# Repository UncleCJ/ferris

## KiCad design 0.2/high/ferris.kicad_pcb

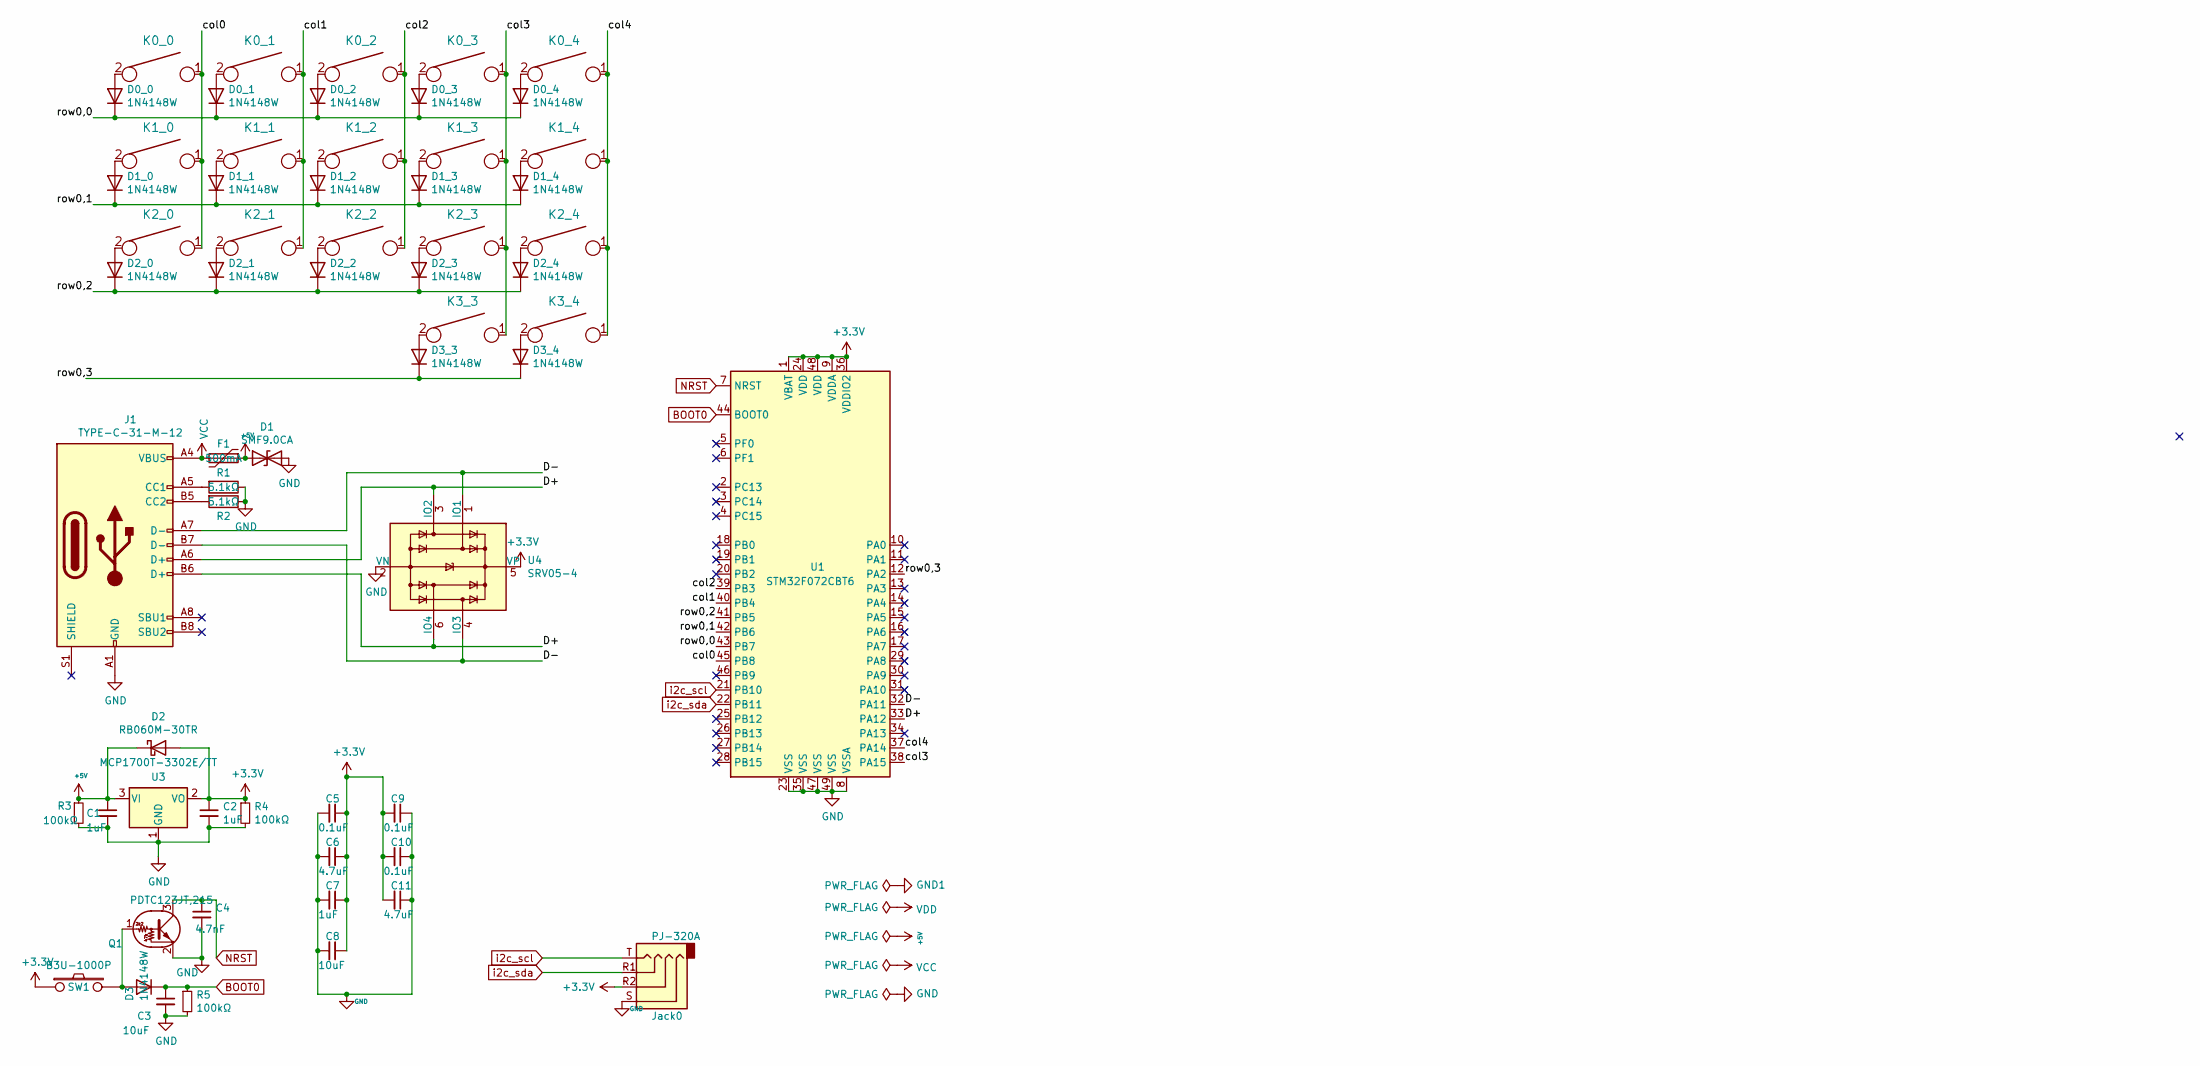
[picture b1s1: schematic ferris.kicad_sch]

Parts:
C1, C2, C7: 1uF; C_0805_2012Metric_Pad1.15x1.40mm_HandSolder; Part Name Capacitor; LCSC Part C28323
C3, C8: 10uF; C_0805_2012Metric_Pad1.15x1.40mm_HandSolder; Part Name Capacitor; LCSC Part C17024
C4: 4.7nF; C_0805_2012Metric_Pad1.15x1.40mm_HandSolder; Part Name Capacitor; LCSC Part C717014
C5, C9, C10: 0.1uF; C_0805_2012Metric_Pad1.15x1.40mm_HandSolder; Part Name Capacitor; LCSC Part C49678
C6, C11: 4.7uF; C_0805_2012Metric_Pad1.15x1.40mm_HandSolder; Part Name Capacitor; LCSC Part C87998
D0_0, D0_1, D0_2, D0_3, D0_4, D1_0, D1_1, D1_2, D1_3, D1_4, D2_0, D2_1, D2_2, D2_3, D2_4, D3, D3_3, D3_4: 1N4148W; D_SOD-123; Part Name Diode; LCSC Part C81598
D1: SMF9.0CA; D_SOD-123; Part Name Bidirectional Diode; LCSC Part C435473
D2: RB060M-30TR; D_SOD-123; Part Name Schottky Barrier Diode; LCSC Part C559324
F1: 500mA; Fuse_1206_3216Metric; Part Name Polyfuse; LCSC Part C151162
J1: TYPE-C-31-M-12; USB_C_Receptacle_HRO_TYPE-C-31-M-12; Part Name USB C; LCSC Part C165948
Jack0: PJ-320A; TRRS-PJ-320A; Part Name TRRS Jack; LCSC Part C12569
K0_0, K0_1, K0_2, K0_3, K0_4, K1_0, K1_1, K1_2, K1_3, K1_4, K2_0, K2_1, K2_2, K2_3, K2_4, K3_3, K3_4: KEYSW; MX; Part Name Key; JLCPCB BOM false
Q1: PDTC123JT,215; SOT-23; Part Name NPN Transistor; LCSC Part C406040
R1, R2: 5.1kΩ; R_0805_2012Metric_Pad1.15x1.40mm_HandSolder; Part Name Resistor; LCSC Part C27834
R3, R4, R5: 100kΩ; R_0805_2012Metric_Pad1.15x1.40mm_HandSolder; Part Name Resistor; LCSC Part C149504
SW1: B3U-1000P; SW_SPST_B3U-1000P; Part Name Reset; LCSC Part C231329
U1: STM32F072CBT6; Dual_MCU_QFP_QFN_48_with_breakout_pins; Part Name MCU; LCSC Part C81720
U3: MCP1700T-3302E/TT; SOT-23; Part Name Dropout Regulator; LCSC Part C39051
U4: SRV05-4; SOT-23-6; Part Name TVS Diode Array; LCSC Part C558418

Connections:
+3V3: C2.1, C5.1, C6.1, C7.1, C8.1, C9.2, C10.2, C11.2, D2.2 (A), Jack0.R2, R4.1, SW1.1, U1.1 (VBAT), U1.9 (VDDA), U1.24 (VDD), U1.36 (VDDIO2), U1.48 (VDD), U3.2 (VO), U4.5 (VP)
+5V: C1.1, D1.1 (A1), D2.1 (K), F1.1, R3.1, U3.3 (VI)
/D+: J1.A6 (D+), J1.B6 (D+), U1.33 (PA12), U4.3 (IO2), U4.6 (IO4)
/D-: J1.A7 (D-), J1.B7 (D-), U1.32 (PA11), U4.1 (IO1), U4.4 (IO3)
/col0: K0_0.1, K1_0.1, K2_0.1, U1.45 (PB8)
/col1: K0_1.1, K1_1.1, K2_1.1, U1.40 (PB4)
/col2: K0_2.1, K1_2.1, K2_2.1, U1.39 (PB3)
/col3: K0_3.1, K1_3.1, K2_3.1, K3_3.1, U1.38 (PA15)
/col4: K0_4.1, K1_4.1, K2_4.1, K3_4.1, U1.37 (PA14)
/row0,0: D0_0.1 (K), D0_1.1 (K), D0_2.1 (K), D0_3.1 (K), D0_4.1 (K), U1.43 (PB7)
/row0,1: D1_0.1 (K), D1_1.1 (K), D1_2.1 (K), D1_3.1 (K), D1_4.1 (K), U1.42 (PB6)
/row0,2: D2_0.1 (K), D2_1.1 (K), D2_2.1 (K), D2_3.1 (K), D2_4.1 (K), U1.41 (PB5)
/row0,3: D3_3.1 (K), D3_4.1 (K), U1.12 (PA2)
BOOT0: C3.1, D3.1 (K), R5.1, U1.44 (BOOT0)
GND: C1.2, C2.2, C3.2, C4.2, C5.2, C6.2, C7.2, C8.2, C9.1, C10.1, C11.1, D1.2 (A2), J1.A1 (GND), J1.A12 (GND), J1.B1 (GND), J1.B12 (GND), Jack0.S, Q1.2 (E), R1.1, R2.1, R3.2, R4.2, R5.2, U1.8 (VSSA), U1.23 (VSS), U1.35 (VSS), U1.47 (VSS), U1.49 (VSS), U3.1 (GND), U4.2 (VN)
NRST: C4.1, Q1.3 (C), U1.7 (NRST)
unnamed: D0_0.2 (A), K0_0.2
unnamed: D0_1.2 (A), K0_1.2
unnamed: D0_2.2 (A), K0_2.2
unnamed: D0_3.2 (A), K0_3.2
unnamed: D0_4.2 (A), K0_4.2
unnamed: D1_0.2 (A), K1_0.2
unnamed: D1_1.2 (A), K1_1.2
unnamed: D1_2.2 (A), K1_2.2
unnamed: D1_3.2 (A), K1_3.2
unnamed: D1_4.2 (A), K1_4.2
unnamed: D2_0.2 (A), K2_0.2
unnamed: D2_1.2 (A), K2_1.2
unnamed: D2_2.2 (A), K2_2.2
unnamed: D2_3.2 (A), K2_3.2
unnamed: D2_4.2 (A), K2_4.2
unnamed: D3.2 (A), Q1.1 (B), SW1.2
unnamed: D3_3.2 (A), K3_3.2
unnamed: D3_4.2 (A), K3_4.2
unnamed: J1.A5 (CC1), R1.2
unnamed: J1.B5 (CC2), R2.2
VCC: F1.2, J1.A4 (VBUS), J1.A9 (VBUS), J1.B4 (VBUS), J1.B9 (VBUS)
i2c_scl: Jack0.T, U1.21 (PB10)
i2c_sda: Jack0.R1, U1.22 (PB11)

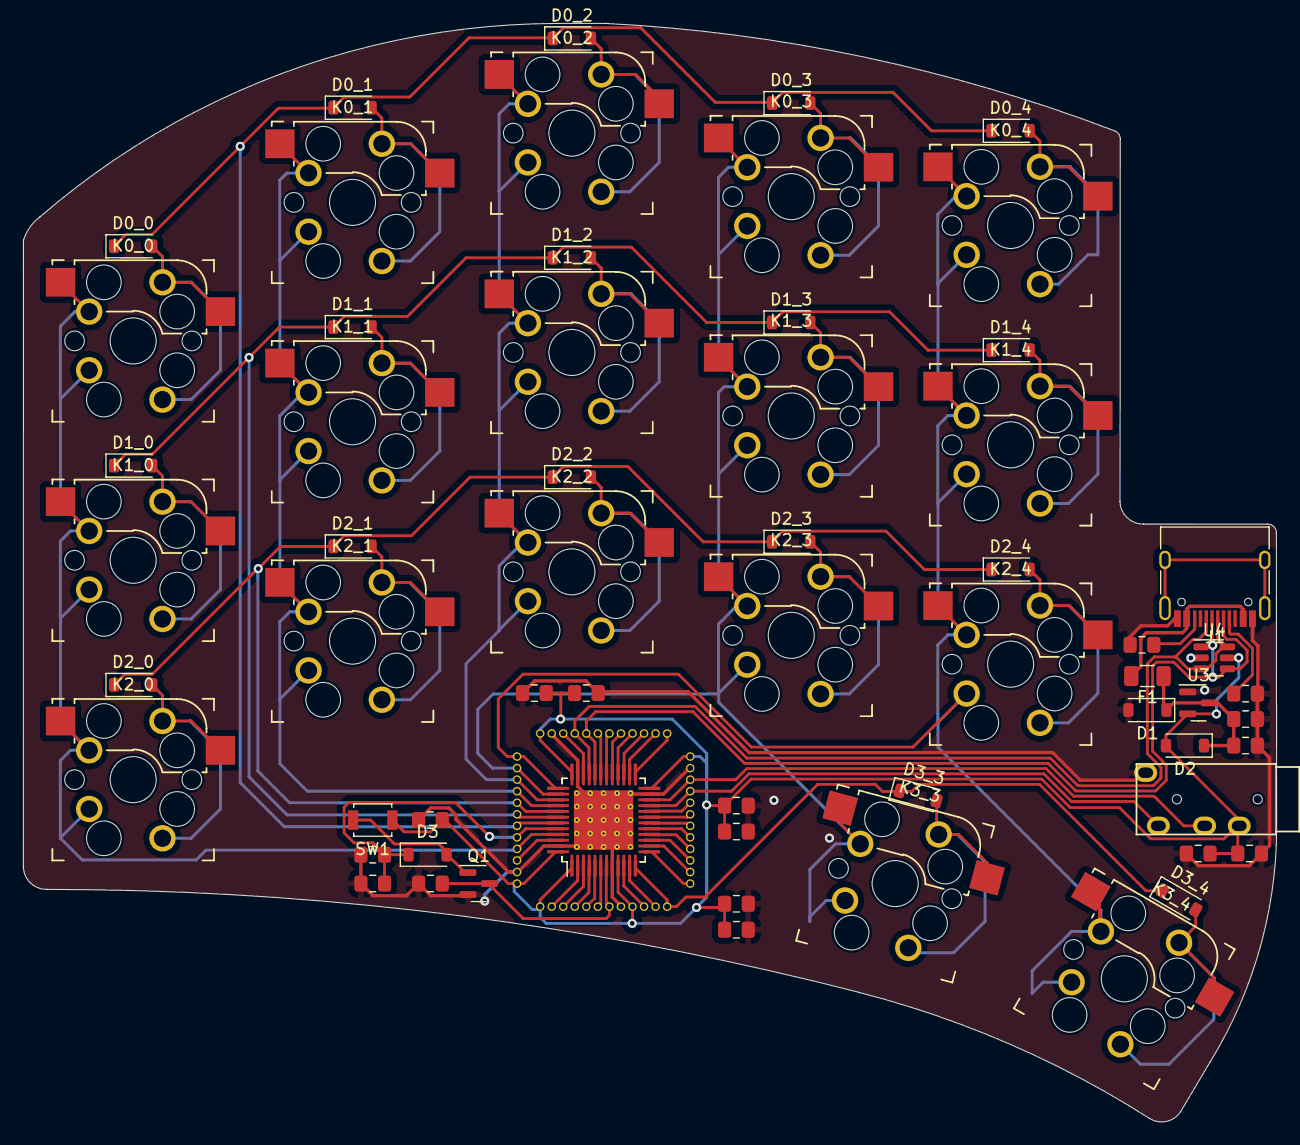
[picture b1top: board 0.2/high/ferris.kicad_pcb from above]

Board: 2 copper layers, 108.5 x 95.2 mm, 61 parts (0 on the bottom side), 39 nets.

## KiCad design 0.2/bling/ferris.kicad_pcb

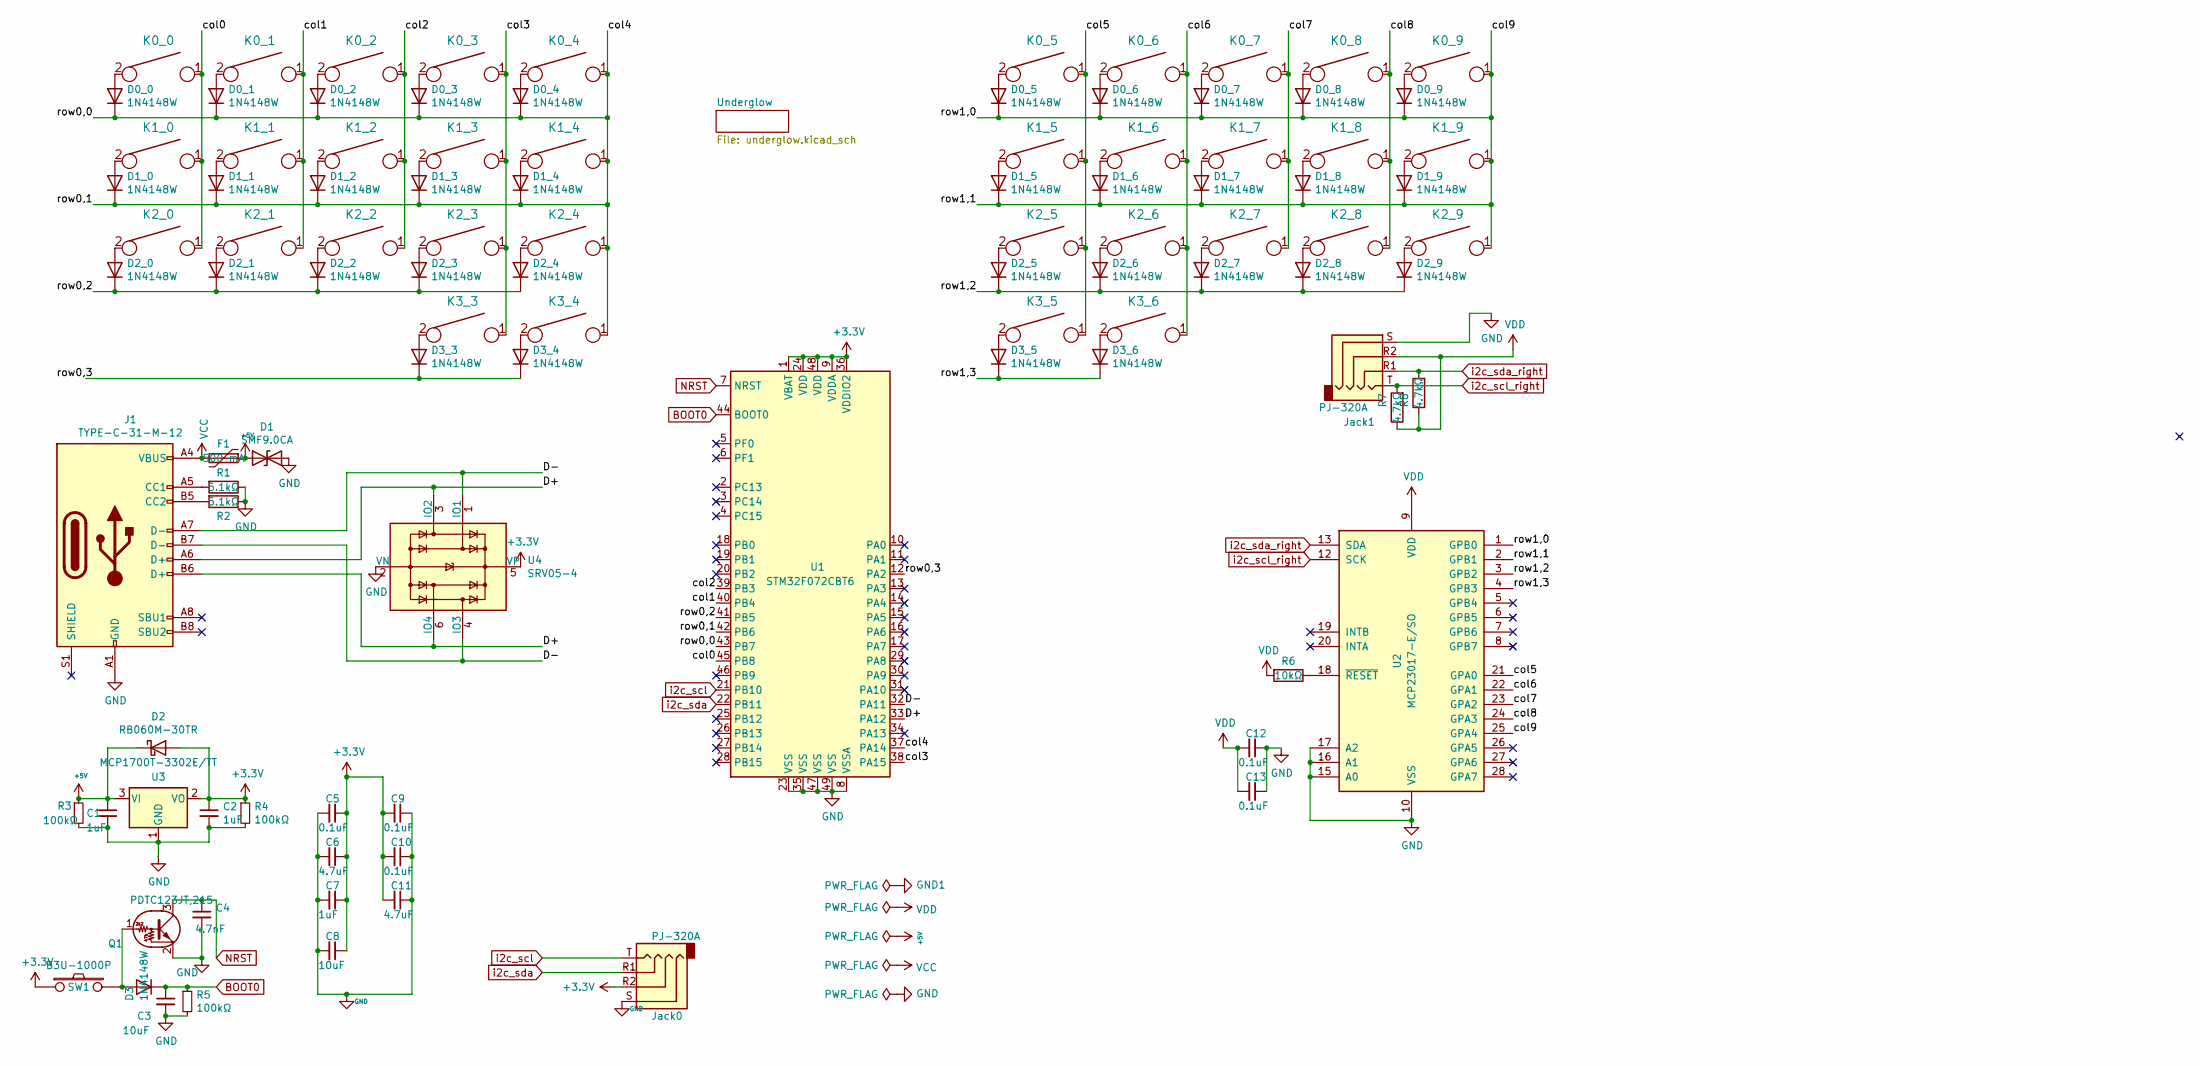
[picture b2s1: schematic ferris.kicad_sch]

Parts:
C1, C2, C7: 1uF; C_0805_2012Metric_Pad1.15x1.40mm_HandSolder; Part Name Capacitor; LCSC Part C28323
C3, C8: 10uF; C_0805_2012Metric_Pad1.15x1.40mm_HandSolder; Part Name Capacitor; LCSC Part C17024
C4: 4.7nF; C_0805_2012Metric_Pad1.15x1.40mm_HandSolder; Part Name Capacitor; LCSC Part C717014
C5, C9, C10, C12, C13: 0.1uF; C_0805_2012Metric_Pad1.15x1.40mm_HandSolder; Part Name Capacitor; LCSC Part C49678
C6, C11: 4.7uF; C_0805_2012Metric_Pad1.15x1.40mm_HandSolder; Part Name Capacitor; LCSC Part C87998
D0_0, D0_1, D0_2, D0_3, D0_4, D0_5, D0_6, D0_7, D0_8, D0_9, D1_0, D1_1, D1_2, D1_3, D1_4, D1_5, D1_6, D1_7, D1_8, D1_9, D2_0, D2_1, D2_2, D2_3, D2_4, D2_5, D2_6, D2_7, D2_8, D2_9, D3, D3_3, D3_4, D3_5, D3_6: 1N4148W; D_SOD-123; Part Name Diode; LCSC Part C81598
D1: SMF9.0CA; D_SOD-123; Part Name Bidirectional Diode; LCSC Part C435473
D2: RB060M-30TR; D_SOD-123; Part Name Schottky Barrier Diode; LCSC Part C559324
F1: 500 mA; Fuse_1206_3216Metric; Part Name Polyfuse; LCSC Part C151162
J1: TYPE-C-31-M-12; USB_C_Receptacle_HRO_TYPE-C-31-M-12; Part Name USB C; LCSC Part C165948
Jack0, Jack1: PJ-320A; TRRS-PJ-320A; Part Name TRRS Jack; LCSC Part C12569
K0_0, K0_1, K0_2, K0_3, K0_4, K0_5, K0_6, K0_7, K0_8, K0_9, K1_0, K1_1, K1_2, K1_3, K1_4, K1_5, K1_6, K1_7, K1_8, K1_9, K2_0, K2_1, K2_2, K2_3, K2_4, K2_5, K2_6, K2_7, K2_8, K2_9, K3_3, K3_4, K3_5, K3_6: KEYSW; Choc_PG1350_Choc_Spacing; Part Name Key; JLCPCB BOM false
Q1: PDTC123JT,215; SOT-23; Part Name NPN Transistor; LCSC Part C406040
R1, R2: 5.1kΩ; R_0805_2012Metric_Pad1.15x1.40mm_HandSolder; Part Name Resistor; LCSC Part C27834
R3, R4, R5: 100kΩ; R_0805_2012Metric_Pad1.15x1.40mm_HandSolder; Part Name Resistor; LCSC Part C149504
R6: 10kΩ; R_0805_2012Metric_Pad1.15x1.40mm_HandSolder; Part Name Resistor; LCSC Part C17414
R7, R8: 4.7kΩ; R_0805_2012Metric_Pad1.15x1.40mm_HandSolder; Part Name Resistor; LCSC Part C17673
SW1: B3U-1000P; SW_SPST_B3U-1000P; Part Name Reset; LCSC Part C231329
U1: STM32F072CBT6; Dual_MCU_QFP_QFN_48_with_breakout_pins; Part Name MCU; LCSC Part C81720
U2: MCP23017-E/SO; SOIC-28W_7.5x17.9mm_P1.27mm; Part Name I/O Expander; LCSC Part C47023
U3: MCP1700T-3302E/TT; SOT-23; Part Name Dropout Regulator; LCSC Part C39051
U4: SRV05-4; SOT-23-6; Part Name TVS Diode Array; LCSC Part C558418

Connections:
+3V3: C2.1, C5.1, C6.1, C7.1, C8.1, C9.2, C10.2, C11.2, D2.2 (A), Jack0.R2, R4.1, SW1.1, U1.1 (VBAT), U1.9 (VDDA), U1.24 (VDD), U1.36 (VDDIO2), U1.48 (VDD), U3.2 (VO), U4.5 (VP); also elsewhere on the board
+5V: C1.1, D1.1 (A1), D2.1 (K), F1.1, R3.1, U3.3 (VI)
/D+: J1.A6 (D+), J1.B6 (D+), U1.33 (PA12), U4.3 (IO2), U4.6 (IO4)
/D-: J1.A7 (D-), J1.B7 (D-), U1.32 (PA11), U4.1 (IO1), U4.4 (IO3)
/col0: K0_0.1, K1_0.1, K2_0.1, U1.45 (PB8)
/col1: K0_1.1, K1_1.1, K2_1.1, U1.40 (PB4)
/col2: K0_2.1, K1_2.1, K2_2.1, U1.39 (PB3)
/col3: K0_3.1, K1_3.1, K2_3.1, K3_3.1, U1.38 (PA15)
/col5: K0_5.1, K1_5.1, K2_5.1, K3_5.1, U2.21 (GPA0)
/col6: K0_6.1, K1_6.1, K2_6.1, K3_6.1, U2.22 (GPA1)
/col7: K0_7.1, K1_7.1, K2_7.1, U2.23 (GPA2)
/col8: K0_8.1, K1_8.1, K2_8.1, U2.24 (GPA3)
/row0,2: D2_0.1 (K), D2_1.1 (K), D2_2.1 (K), D2_3.1 (K), D2_4.1 (K), U1.41 (PB5)
/row0,3: D3_3.1 (K), D3_4.1 (K), U1.12 (PA2)
/row1,2: D2_5.1 (K), D2_6.1 (K), D2_7.1 (K), D2_8.1 (K), D2_9.1 (K), U2.3 (GPB2)
/row1,3: D3_5.1 (K), D3_6.1 (K), U2.4 (GPB3)
BOOT0: C3.1, D3.1 (K), R5.1, U1.44 (BOOT0)
GND: C1.2, C2.2, C3.2, C4.2, C5.2, C6.2, C7.2, C8.2, C9.1, C10.1, C11.1, C12.1, C13.1, D1.2 (A2), J1.A1 (GND), J1.A12 (GND), J1.B1 (GND), J1.B12 (GND), Jack0.S, Jack1.S, Q1.2 (E), R1.1, R2.1, R3.2, R4.2, R5.2, U1.8 (VSSA), U1.23 (VSS), U1.35 (VSS), U1.47 (VSS), U1.49 (VSS), U2.10 (VSS), U2.15 (A0), U2.16 (A1), U2.17 (A2), U3.1 (GND), U4.2 (VN); also elsewhere on the board
NRST: C4.1, Q1.3 (C), U1.7 (NRST)
unnamed: D0_0.2 (A), K0_0.2
unnamed: D0_1.2 (A), K0_1.2
unnamed: D0_2.2 (A), K0_2.2
unnamed: D0_3.2 (A), K0_3.2
unnamed: D0_4.2 (A), K0_4.2
unnamed: D0_5.2 (A), K0_5.2
unnamed: D0_6.2 (A), K0_6.2
unnamed: D0_7.2 (A), K0_7.2
unnamed: D0_8.2 (A), K0_8.2
unnamed: D0_9.2 (A), K0_9.2
unnamed: D1_0.2 (A), K1_0.2
unnamed: D1_1.2 (A), K1_1.2
unnamed: D1_2.2 (A), K1_2.2
unnamed: D1_3.2 (A), K1_3.2
unnamed: D1_4.2 (A), K1_4.2
unnamed: D1_5.2 (A), K1_5.2
unnamed: D1_6.2 (A), K1_6.2
unnamed: D1_7.2 (A), K1_7.2
unnamed: D1_8.2 (A), K1_8.2
unnamed: D1_9.2 (A), K1_9.2
unnamed: D2_0.2 (A), K2_0.2
unnamed: D2_1.2 (A), K2_1.2
unnamed: D2_2.2 (A), K2_2.2
unnamed: D2_3.2 (A), K2_3.2
unnamed: D2_4.2 (A), K2_4.2
unnamed: D2_5.2 (A), K2_5.2
unnamed: D2_6.2 (A), K2_6.2
unnamed: D2_7.2 (A), K2_7.2
unnamed: D2_8.2 (A), K2_8.2
unnamed: D2_9.2 (A), K2_9.2
unnamed: D3.2 (A), Q1.1 (B), SW1.2
unnamed: D3_3.2 (A), K3_3.2
unnamed: D3_4.2 (A), K3_4.2
unnamed: D3_5.2 (A), K3_5.2
unnamed: D3_6.2 (A), K3_6.2
unnamed: J1.A5 (CC1), R1.2
unnamed: J1.B5 (CC2), R2.2
unnamed: R6.1, U2.18 (~RESET)
VCC: F1.2, J1.A4 (VBUS), J1.A9 (VBUS), J1.B4 (VBUS), J1.B9 (VBUS)
VDD: C12.2, C13.2, Jack1.R2, R6.2, R7.1, R8.1, U2.9 (VDD); also elsewhere on the board
i2c_scl: Jack0.T, U1.21 (PB10); also elsewhere on the board
i2c_scl_right: Jack1.T, R7.2, U2.12 (SCK); also elsewhere on the board
i2c_sda: Jack0.R1, U1.22 (PB11); also elsewhere on the board
i2c_sda_right: Jack1.R1, R8.2, U2.13 (SDA); also elsewhere on the board

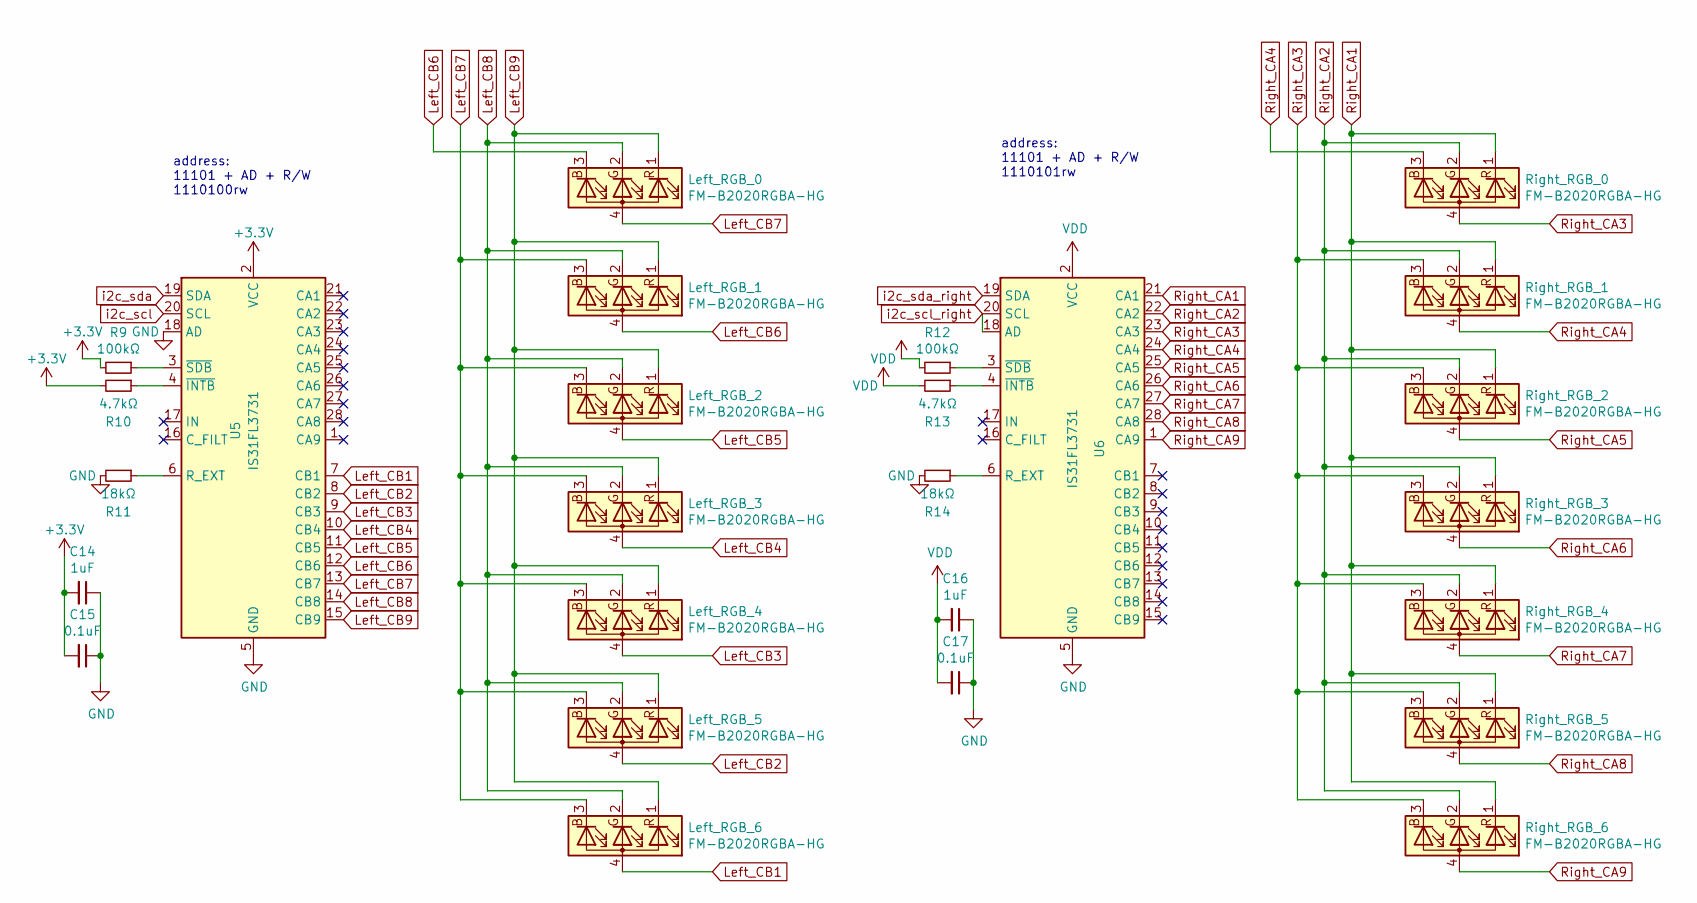
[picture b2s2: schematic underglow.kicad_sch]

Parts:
C14, C16: 1uF; C_0805_2012Metric_Pad1.15x1.40mm_HandSolder; Part Name Capacitor; LCSC Part C28323
C15, C17: 0.1uF; C_0805_2012Metric_Pad1.15x1.40mm_HandSolder; Part Name Capacitor; LCSC Part C49678
Left_RGB_0, Left_RGB_1, Left_RGB_2, Left_RGB_3, Left_RGB_4, Left_RGB_5, Left_RGB_6: FM-B2020RGBA-HG; LED_RGB_FM-B2020RGBA-HG; Part Name RGB LED; LCSC Part C108793
R9, R12: 100kΩ; R_0805_2012Metric_Pad1.15x1.40mm_HandSolder; Part Name Resistor; LCSC Part C149504
R10, R13: 4.7kΩ; R_0805_2012Metric_Pad1.15x1.40mm_HandSolder; Part Name Resistor; LCSC Part C17673
R11, R14: 18kΩ; R_0805_2012Metric_Pad1.15x1.40mm_HandSolder; Part Name Resistor; LCSC Part C25622
Right_RGB_0, Right_RGB_1, Right_RGB_2, Right_RGB_3, Right_RGB_4, Right_RGB_5, Right_RGB_6: FM-B2020RGBA-HG; LED_RGB_FM-B2020RGBA-HG; Part Name RGB LED; LCSC Part C108793
U5, U6: IS31FL3731; QFN-28-1EP_4x4mm_P0.4mm_EP2.3x2.3mm_ThermalVias; Part Name LED Driver; LCSC Part C191206

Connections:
+3V3: C14.2, C15.2, R9.2, R10.2, U5.2 (VCC); also elsewhere on the board
GND: C14.1, C15.1, C16.1, C17.1, R11.2, R14.2, U5.5 (GND), U5.18 (AD), U5.29 (GND), U6.5 (GND), U6.29 (GND); also elsewhere on the board
Left_CB1: Left_RGB_6.4 (A), U5.7 (CB1)
Left_CB2: Left_RGB_5.4 (A), U5.8 (CB2)
Left_CB3: Left_RGB_4.4 (A), U5.9 (CB3)
Left_CB4: Left_RGB_3.4 (A), U5.10 (CB4)
Left_CB5: Left_RGB_2.4 (A), U5.11 (CB5)
Left_CB6: Left_RGB_0.3 (BK), Left_RGB_1.4 (A), U5.12 (CB6)
Left_CB7: Left_RGB_0.4 (A), Left_RGB_1.3 (BK), Left_RGB_2.3 (BK), Left_RGB_3.3 (BK), Left_RGB_4.3 (BK), Left_RGB_5.3 (BK), Left_RGB_6.3 (BK), U5.13 (CB7)
Left_CB8: Left_RGB_0.2 (GK), Left_RGB_1.2 (GK), Left_RGB_2.2 (GK), Left_RGB_3.2 (GK), Left_RGB_4.2 (GK), Left_RGB_5.2 (GK), Left_RGB_6.2 (GK), U5.14 (CB8)
Left_CB9: Left_RGB_0.1 (RK), Left_RGB_1.1 (RK), Left_RGB_2.1 (RK), Left_RGB_3.1 (RK), Left_RGB_4.1 (RK), Left_RGB_5.1 (RK), Left_RGB_6.1 (RK), U5.15 (CB9)
unnamed: R9.1, U5.3 (~SDB)
unnamed: R10.1, U5.4 (~INTB)
unnamed: R11.1, U5.6 (R_EXT)
unnamed: R12.1, U6.3 (~SDB)
unnamed: R13.1, U6.4 (~INTB)
unnamed: R14.1, U6.6 (R_EXT)
Right_CA1: Right_RGB_0.1 (RK), Right_RGB_1.1 (RK), Right_RGB_2.1 (RK), Right_RGB_3.1 (RK), Right_RGB_4.1 (RK), Right_RGB_5.1 (RK), Right_RGB_6.1 (RK), U6.21 (CA1)
Right_CA2: Right_RGB_0.2 (GK), Right_RGB_1.2 (GK), Right_RGB_2.2 (GK), Right_RGB_3.2 (GK), Right_RGB_4.2 (GK), Right_RGB_5.2 (GK), Right_RGB_6.2 (GK), U6.22 (CA2)
Right_CA3: Right_RGB_0.4 (A), Right_RGB_1.3 (BK), Right_RGB_2.3 (BK), Right_RGB_3.3 (BK), Right_RGB_4.3 (BK), Right_RGB_5.3 (BK), Right_RGB_6.3 (BK), U6.23 (CA3)
Right_CA4: Right_RGB_0.3 (BK), Right_RGB_1.4 (A), U6.24 (CA4)
Right_CA5: Right_RGB_2.4 (A), U6.25 (CA5)
Right_CA6: Right_RGB_3.4 (A), U6.26 (CA6)
Right_CA7: Right_RGB_4.4 (A), U6.27 (CA7)
Right_CA8: Right_RGB_5.4 (A), U6.28 (CA8)
Right_CA9: Right_RGB_6.4 (A), U6.1 (CA9)
VDD: C16.2, C17.2, R12.2, R13.2, U6.2 (VCC); also elsewhere on the board
i2c_scl: U5.20 (SCL); also elsewhere on the board
i2c_scl_right: U6.18 (AD), U6.20 (SCL); also elsewhere on the board
i2c_sda: U5.19 (SDA); also elsewhere on the board
i2c_sda_right: U6.19 (SDA); also elsewhere on the board

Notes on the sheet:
address: 11101 + AD + R/W 1110100rw
address: 11101 + AD + R/W 1110101rw

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
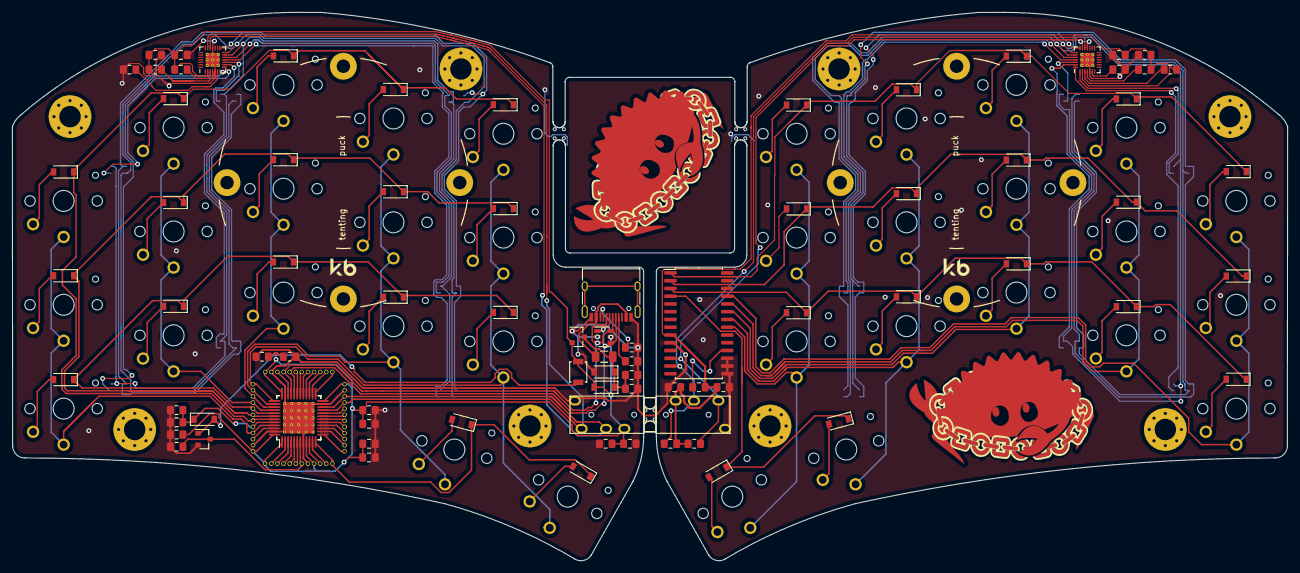
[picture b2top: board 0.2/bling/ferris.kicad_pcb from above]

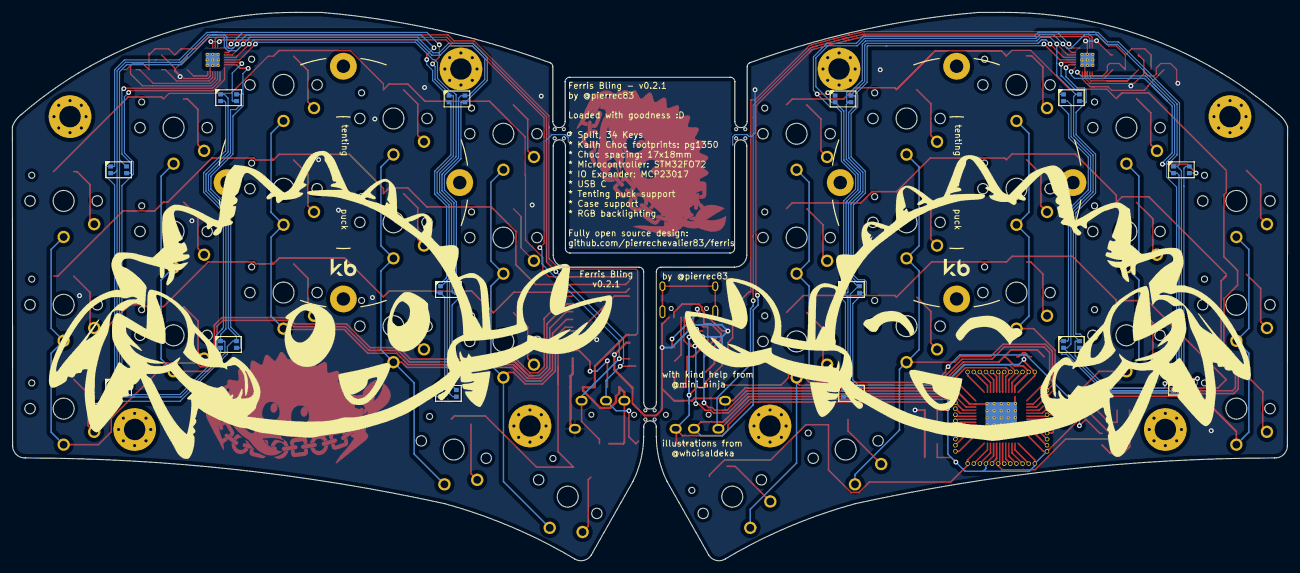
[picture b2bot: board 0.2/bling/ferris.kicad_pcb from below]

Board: 2 copper layers, 208.8 x 89.8 mm, 131 parts (14 on the bottom side), 93 nets.

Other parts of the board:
mouse-bite-2mm-slot, mouse-bite-2mm-slot#2, mouse-bite-2mm-slot#3: VAL**; mouse-bite-2mm-slot-with-space-for-track

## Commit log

2023-08-05 Begin attempting to fix schematic bug
2023-08-05 Attempt to replicate fixing hole clearances
2023-08-05 Attempt to replicate df923a93 Make all mouse bites 5mm
2023-08-05 Update to KiCad 7.0
    ... and prune outdated project files (need to check)
2023-08-05 Add daprice_keyswitches footprint library as submodule
2023-08-06 Again, fix schematic bug connecting rows directly to rightmost column
2023-08-06 Again, initiate reversible
2023-08-06 Successfully routed reversible MX footprints
2023-08-07 Fix DRC violations down to 163
    Mainly hole clearances, would need to fix the 5mm breakaway tab and perhaps solder mask clearances
2023-08-07 Fix more violations, down to 128
    Mainly updated footprints where needed, kbd library is still not loaded, and various are missing from Resistor/Capacitor_SMD?
2023-08-07 Strip down board
    Fix a couple of 3D models
    Should do this for the complete board
